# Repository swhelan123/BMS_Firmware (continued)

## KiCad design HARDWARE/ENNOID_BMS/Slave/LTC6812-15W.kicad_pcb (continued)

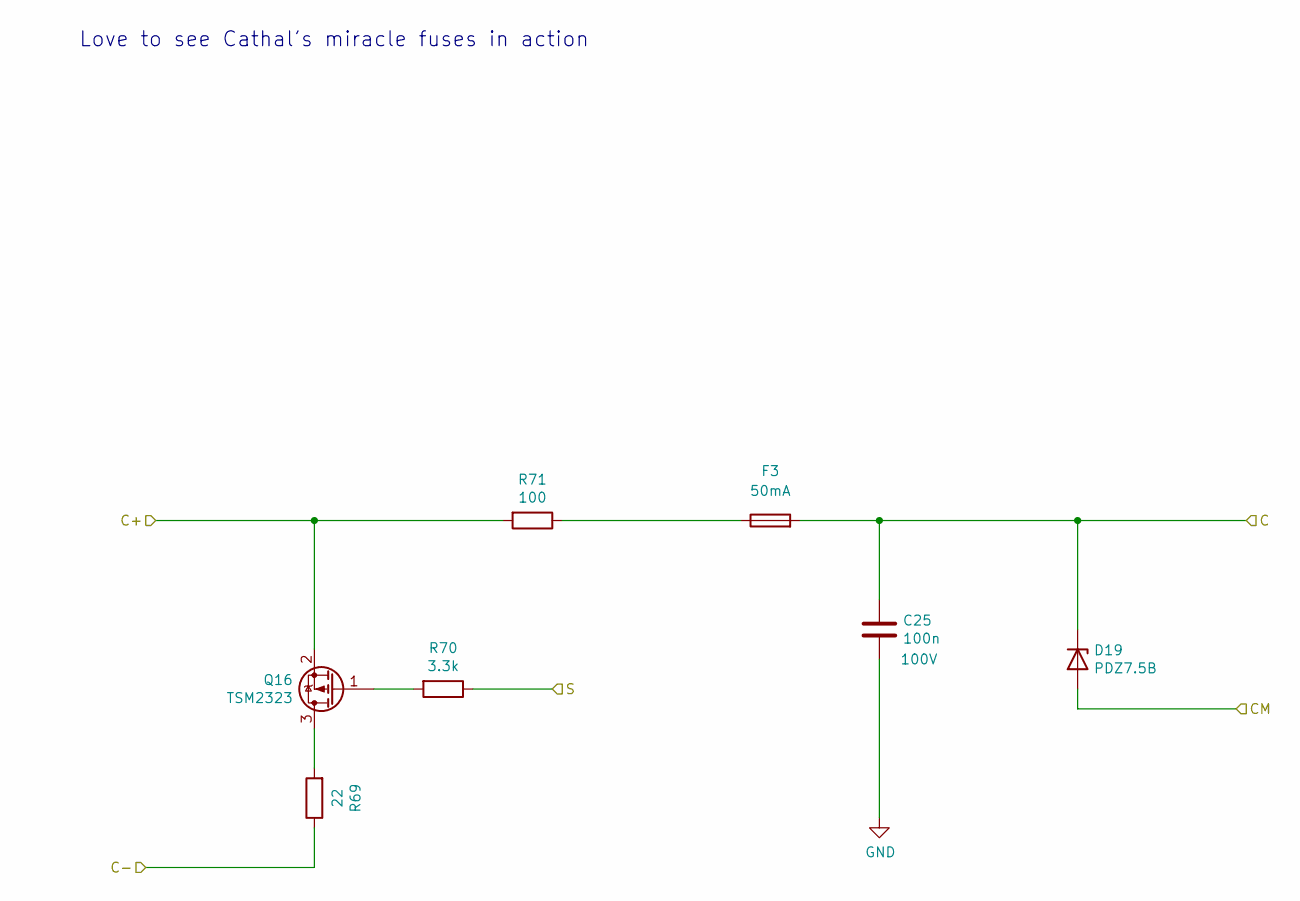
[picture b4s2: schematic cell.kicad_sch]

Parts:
C25: 100n; C_0603_1608Metric; Voltage 100V; Part Number GRM188R72A104KA35D
D19: PDZ7.5B; D_SOD-323; Part Number PDZ7.5B
F3: 50mA; Fuse_1206_3216Metric; Part Number 3413.0002.11
Q16: TSM2323; SOT-23; Part Number TSM2323CX RFG
R69: 22; R_2512_6332Metric; Part Number AC2512JK-7W22RL
R70: 3.3k; R_0508_1220Metric; Part Number WK73R2ATTD3301F
R71: 100; R_0805_2012Metric; Part Number CRCW0805100RFKEAHP

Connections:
/cell14/C: D19.2 (A); also elsewhere on the board
/cell15/C: C25.2, D19.1 (K), F3.2; also elsewhere on the board
/cell15/S: R70.1; also elsewhere on the board
Cell_1-: C25.1; also elsewhere on the board
Cell_14+: R69.1; also elsewhere on the board
Cell_15+: Q16.2 (S), R71.2; also elsewhere on the board
unnamed: F3.1, R71.1
unnamed: Q16.3 (D), R69.2
unnamed: Q16.1 (G), R70.2

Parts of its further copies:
C11, C12, C13, C14, C15, C16, C17, C18, C19, C20, C21, C22, C23, C24: 100n; C_0603_1608Metric; Voltage 100V; Part Number GRM188R72A104KA35D
D5, D6, D7, D8, D9, D10, D11, D12, D13, D14, D15, D16, D17, D18: PDZ7.5B; D_SOD-323; Part Number PDZ7.5B
F5, F7, F9, F11, F13, F15, F20, F22, F24, F26, F28, F30, F32, F34: 50mA; Fuse_1206_3216Metric; Part Number 3413.0002.11
Q2, Q3, Q4, Q5, Q6, Q7, Q8, Q9, Q10, Q11, Q12, Q13, Q14, Q15: TSM2323; SOT-23; Part Number TSM2323CX RFG
R13, R17, R21, R25, R29, R33, R37, R41, R45, R49, R53, R57, R61, R65: 22; R_2512_6332Metric; Part Number AC2512JK-7W22RL
R14, R18, R22, R26, R30, R34, R38, R42, R46, R50, R54, R58, R62, R66: 3.3k; R_0508_1220Metric; Part Number WK73R2ATTD3301F
R15, R19, R23, R27, R31, R35, R39, R43, R47, R51, R55, R59, R63, R67: 100; R_0805_2012Metric; Part Number CRCW0805100RFKEAHP

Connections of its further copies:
/cell1/C: C11.2, D5.1 (K), D6.2 (A), F34.2; also elsewhere on the board
/cell1/S: R14.1; also elsewhere on the board
/cell2/C: C12.2, D6.1 (K), D7.2 (A), F32.2; also elsewhere on the board
/cell2/S: R18.1; also elsewhere on the board
/cell3/C: C13.2, D7.1 (K), D8.2 (A), F30.2; also elsewhere on the board
/cell3/S: R22.1; also elsewhere on the board
/cell4/C: C14.2, D8.1 (K), D9.2 (A), F28.2; also elsewhere on the board
/cell4/S: R26.1; also elsewhere on the board
/cell5/C: C15.2, D9.1 (K), D10.2 (A), F26.2; also elsewhere on the board
/cell5/S: R30.1; also elsewhere on the board
/cell6/C: C16.2, D10.1 (K), D11.2 (A), F24.2; also elsewhere on the board
/cell6/S: R34.1; also elsewhere on the board
/cell7/C: C17.2, D11.1 (K), D12.2 (A), F22.2; also elsewhere on the board
/cell7/S: R38.1; also elsewhere on the board
/cell8/C: C18.2, D12.1 (K), D13.2 (A), F20.2; also elsewhere on the board
/cell8/S: R42.1; also elsewhere on the board
/cell9/S: R46.1; also elsewhere on the board
/cell10/C: C20.2, D14.1 (K), D15.2 (A), F13.2; also elsewhere on the board
/cell10/CM: C19.2, D13.1 (K), D14.2 (A), F15.2; also elsewhere on the board
/cell10/S: R50.1; also elsewhere on the board
/cell11/C: C21.2, D15.1 (K), D16.2 (A), F11.2; also elsewhere on the board
/cell11/S: R54.1; also elsewhere on the board
/cell12/C: C22.2, D16.1 (K), D17.2 (A), F9.2; also elsewhere on the board
/cell12/S: R58.1; also elsewhere on the board
/cell13/C: C23.2, D17.1 (K), D18.2 (A), F7.2; also elsewhere on the board
/cell13/S: R62.1; also elsewhere on the board
/cell14/C: C24.2, D18.1 (K), F5.2; also elsewhere on the board
/cell14/S: R66.1; also elsewhere on the board
Cell_1+: Q2.2 (S), R15.2, R17.1; also elsewhere on the board
Cell_1-: C11.1, C12.1, C13.1, C14.1, C15.1, C16.1, C17.1, C18.1, C19.1, C20.1, C21.1, C22.1, C23.1, C24.1, D5.2 (A), R13.1; also elsewhere on the board
Cell_2+: Q3.2 (S), R19.2, R21.1; also elsewhere on the board
Cell_3+: Q4.2 (S), R23.2, R25.1; also elsewhere on the board
Cell_4+: Q5.2 (S), R27.2, R29.1; also elsewhere on the board
Cell_5+: Q6.2 (S), R31.2, R33.1; also elsewhere on the board
Cell_6+: Q7.2 (S), R35.2, R37.1; also elsewhere on the board
Cell_7+: Q8.2 (S), R39.2, R41.1; also elsewhere on the board
Cell_8+: Q9.2 (S), R43.2, R45.1; also elsewhere on the board
Cell_9+: Q10.2 (S), R47.2, R49.1; also elsewhere on the board
Cell_10+: Q11.2 (S), R51.2, R53.1; also elsewhere on the board
Cell_11+: Q12.2 (S), R55.2, R57.1; also elsewhere on the board
Cell_12+: Q13.2 (S), R59.2, R61.1; also elsewhere on the board
Cell_13+: Q14.2 (S), R63.2, R65.1; also elsewhere on the board
Cell_14+: Q15.2 (S), R67.2; also elsewhere on the board
unnamed: F5.1, R67.1
unnamed: F7.1, R63.1
unnamed: F9.1, R59.1
unnamed: F11.1, R55.1
unnamed: F13.1, R51.1
unnamed: F15.1, R47.1
unnamed: F20.1, R43.1
unnamed: F22.1, R39.1
unnamed: F24.1, R35.1
unnamed: F26.1, R31.1
unnamed: F28.1, R27.1
unnamed: F30.1, R23.1
unnamed: F32.1, R19.1
unnamed: F34.1, R15.1
unnamed: Q2.3 (D), R13.2
unnamed: Q2.1 (G), R14.2
unnamed: Q3.3 (D), R17.2
unnamed: Q3.1 (G), R18.2
unnamed: Q4.3 (D), R21.2
unnamed: Q4.1 (G), R22.2
unnamed: Q5.3 (D), R25.2
unnamed: Q5.1 (G), R26.2
unnamed: Q6.3 (D), R29.2
unnamed: Q6.1 (G), R30.2
unnamed: Q7.3 (D), R33.2
unnamed: Q7.1 (G), R34.2
unnamed: Q8.3 (D), R37.2
unnamed: Q8.1 (G), R38.2
unnamed: Q9.3 (D), R41.2
unnamed: Q9.1 (G), R42.2
unnamed: Q10.3 (D), R45.2
unnamed: Q10.1 (G), R46.2
unnamed: Q11.3 (D), R49.2
unnamed: Q11.1 (G), R50.2
unnamed: Q12.3 (D), R53.2
unnamed: Q12.1 (G), R54.2
unnamed: Q13.3 (D), R57.2
unnamed: Q13.1 (G), R58.2
unnamed: Q14.3 (D), R61.2
unnamed: Q14.1 (G), R62.2
unnamed: Q15.3 (D), R65.2
unnamed: Q15.1 (G), R66.2

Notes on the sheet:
Love to see Cathal's miracle fuses in action

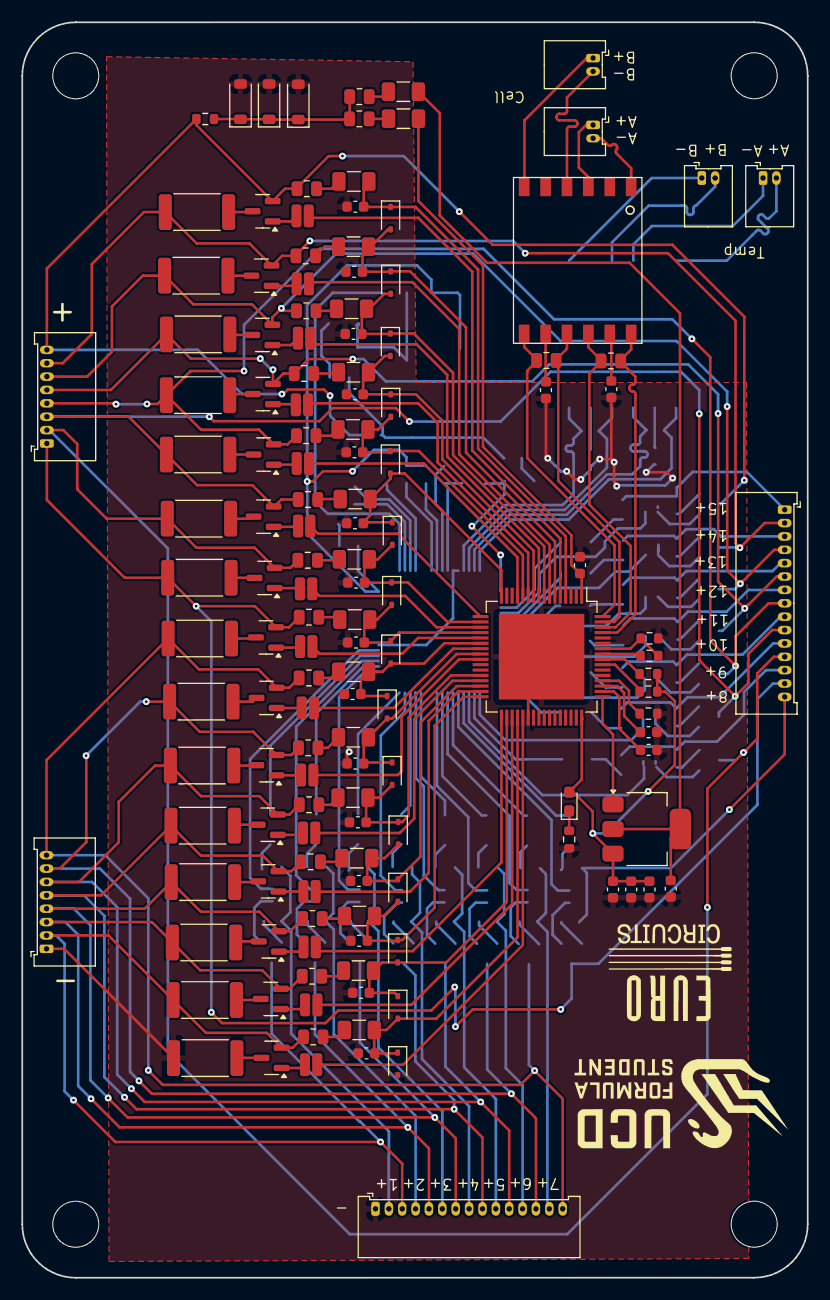
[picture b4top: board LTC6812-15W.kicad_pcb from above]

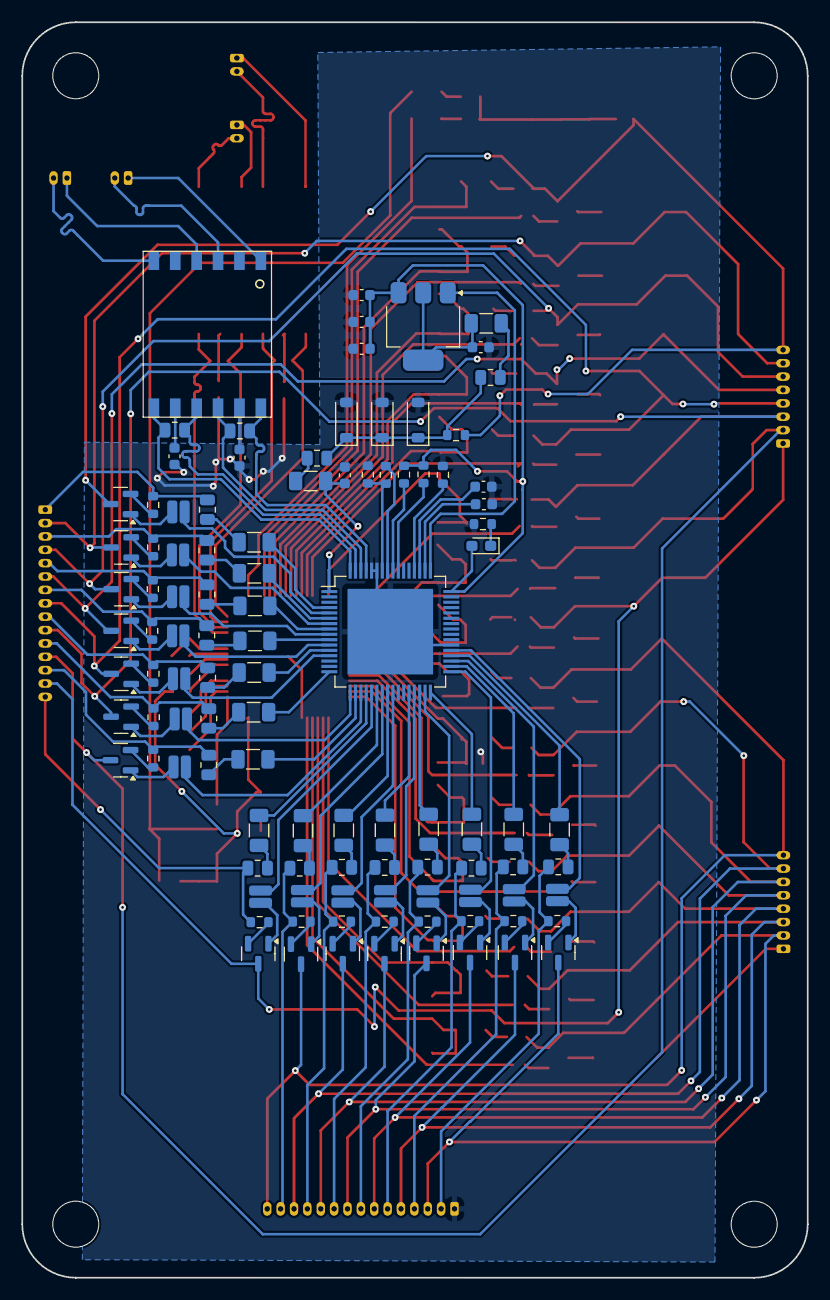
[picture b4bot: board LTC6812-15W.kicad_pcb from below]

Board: 2 copper layers, 73.4 x 117.4 mm, 246 parts (104 on the bottom side), 231 nets.

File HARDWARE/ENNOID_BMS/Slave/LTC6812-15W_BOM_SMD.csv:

Reference,Qty,Value,DNP,Footprint,Datasheet,Part Number
"C1,C4,C10,C11,C12,C13,C14,C15,C16,C17,C18,C19,C20,C21,C22,C23,C24,C25,C28",19,100n,,Capacitor_SMD:C_0603_1608Metric,https://pim.murata.com/asset/pim4/ceramicCapacitorSMD/GRM188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,GRM188R72A104KA35D
"C2,C3,C5,C6,C7,C26,C27,C29,C30,C31",10,1uF,,Capacitor_SMD:C_0603_1608Metric,https://mm.digikey.com/Volume0/opasdata/d220001/medias/docus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,CL10B105KP8NNNC
"C8,C9,C32,C33",4,100p,,Capacitor_SMD:C_0603_1608Metric,https://pim.murata.com/asset/pim4/ceramicCapacitorSMD/GRM188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,GRM1885C1H101JA01D
"D1,D2,D20,D21",4,1N4148W,,Diode_SMD:D_SOD-123,https://www.mouser.ie/datasheet/3/175/1/BAV16W_1N4148W.pdf,1N4148W-7-F
"D3,D22",2,MMSZ5268BT1G,,Diode_SMD:D_SOD-123,https://www.onsemi.com/pub/Collateral/MMSZ5221BT1-D.PDF,MMSZ5268BT1G
"D4,D23",2,LED,,LED_SMD:LED_0603_1608Metric_Pad1.05x0.95mm_HandSolder,https://www.vishay.com/doc?84393,VLMTG1400-GS08
"D5,D6,D7,D8,D9,D10,D11,D12,D13,D14,D15,D16,D17,D18,D19",15,PDZ7.5B,,Diode_SMD:D_SOD-323,https://assets.nexperia.com/documents/data-sheet/PDZ-B_SER.pdf,PDZ7.5B
"F1,F2,F3,F20,F21,F22,F23,F24,F25,F26,F27,F28,F29,F30,F31,F32",16,5A,,ENNOID:FUSC10948X488N,https://4donline.ihs.com/images/VipMasterIC/IC/LFSI/LFSI-S-A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,0885005.DR
"FB1,FB2",2,33,,Resistor_SMD:R_0603_1608Metric,https://www.mouser.ie/datasheet/3/76/1/ENFA0003.pdf,BLM18PG330SN1D
"Q1,Q17",2,DZTT5551,,Package_TO_SOT_SMD:SOT-223,https://www.mouser.ie/datasheet/3/175/1/ds31219.pdf,DZT5551-13
"Q2,Q3,Q4,Q5,Q6,Q7,Q8,Q9,Q10,Q11,Q12,Q13,Q14,Q15,Q16",15,TSM2323,,Package_TO_SOT_SMD:SOT-23,https://www.taiwansemi.com/assets/datasheet/pdf.php?pn=TSM2323CX,TSM2323
"Q18,Q19,Q20,Q21,Q22,Q23,Q24,Q25,Q26,Q27,Q28,Q29,Q30,Q31,Q32",15,2N7002,,Package_TO_SOT_SMD:SOT-23,https://www.onsemi.com/pub/Collateral/NDS7002A-D.PDF,2N7002
"R1,R3,R8,R9,R15,R19,R23,R27,R31,R35,R39,R43,R47,R51,R55,R59,R63,R67,R71,R74,R76,R81,R82,R84,R85,R86,R87,R88,R89,R90,R91,R92,R93,R94,R95,R96,R98,R99",38,100,,Resistor_SMD:R_0603_1608Metric,https://www.vishay.com/docs/20035/dcrcwe3.pdf,CRCW0603100RFKEA
"R2,R75",2,806,,Resistor_SMD:R_0603_1608Metric,https://www.vishay.com/docs/20035/dcrcwe3.pdf,CRCW0603806RFKEA
"R4,R77",2,1M,,Resistor_SMD:R_0603_1608Metric,https://www.vishay.com/docs/20035/dcrcwe3.pdf,CRCW06031M00FKEA
"R5,R10,R78,R83",4,1.2k,,Resistor_SMD:R_0603_1608Metric,https://www.vishay.com/docs/20035/dcrcwe3.pdf,CRCW06031K20FKEA
"R6,R7,R79,R80",4,0,,Resistor_SMD:R_0603_1608Metric,https://www.vishay.com/docs/20035/dcrcwe3.pdf,CRCW06030000Z0EA
"R11,R12,R16,R20,R24,R28,R32,R36,R40,R44,R48,R52,R56,R60,R64",15,680,,Resistor_SMD:R_0603_1608Metric,https://www.vishay.com/docs/20035/dcrcwe3.pdf,CRCW0603680RFKEA
"R13,R17,R21,R25,R29,R33,R37,R41,R45,R49,R53,R57,R61,R65,R69",15,22,,Resistor_SMD:R_2512_6332Metric,https://www.mouser.ie/datasheet/3/508/1/PYu-AC_51_RoHS_L_11.pdf,AC2512JK-7W22RL
"R14,R18,R22,R26,R30,R34,R38,R42,R46,R50,R54,R58,R62,R66,R68,R70,R72,R73,R97,R100,R101,R102,R103,R104,R105,R106,R107,R108,R109,R110",30,3.3k,,Resistor_SMD:R_0603_1608Metric,https://www.vishay.com/docs/20035/dcrcwe3.pdf,CRCW06033K30FKEA
"TR1,TR2",2,HM2102NL,,ENNOID:HM2102NL,https://www.mouser.ie/datasheet/3/508/1/HM2102NL.pdf,HM2102NL
"U1,U2",2,LTC6812-1,,ENNOID:TQFP-64-1EP_10x10mm_P0.5mm_EP8x8mm,https://www.analog.com/media/en/technical-documentation/data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,LTC6812-1

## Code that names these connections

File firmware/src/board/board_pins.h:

/* board_pins.h — STM32F303VC pin assignments for this hardware revision.
 *
 * Conventions:
 *   GPIOx_PIN_n  where x = port letter, n = pin number
 *   _AF_n        alternate function number (from STM32F303 datasheet Table 14)
 *
 * OQ items are OPEN QUESTION fields still awaiting hardware confirmation.
 */
#pragma once

/* ── SPI1 — shared isoSPI bus ─────────────────────────────────────────────── */
#define SPI_PORT            GPIOA
#define SPI_SCK_PIN         5u      /* PA5  — AF5: SPI1_SCK  */
#define SPI_MISO_PIN        6u      /* PA6  — AF5: SPI1_MISO */
#define SPI_MOSI_PIN        7u      /* PA7  — AF5: SPI1_MOSI */
#define SPI_AF              5u

/* ── SPI1 chip-selects (manual GPIO, active-low, idle HIGH) ──────────────── */
#define CS_CELL_PORT        GPIOA
#define CS_CELL_PIN         4u      /* PA4  — CS for CELL-chain LTC6820 */

#define CS_TEMP_PORT        GPIOB
#define CS_TEMP_PIN         12u     /* PB12 — CS for TEMP-chain LTC6820 */

/* ── USART2 — USB-serial bridge (CP2104) ─────────────────────────────────── */
#define UART_PORT           GPIOA
#define UART_TX_PIN         2u      /* PA2  — AF7: USART2_TX */
#define UART_RX_PIN         3u      /* PA3  — AF7: USART2_RX */
#define UART_AF             7u

/* ── I2C2 — ISL28022 power monitor ───────────────────────────────────────── */
#define I2C_PORT            GPIOA
#define I2C_SCL_PIN         9u      /* PA9  — AF4: I2C2_SCL */
#define I2C_SDA_PIN         10u     /* PA10 — AF4: I2C2_SDA */
#define I2C_AF              4u

/* ISL28022 I2C address: A0 and A1 pins are unconnected (float → pulled low).
 * Default address = 0x40 (A1=0, A0=0). Verify on board before first I2C test. */
#define ISL28022_I2C_ADDR   (0x40u)

/* ── ADC1 — Vpack load-side voltage ─────────────────────────────────────── */
#define VPACK_ADC_PORT      GPIOA
#define VPACK_ADC_PIN       1u      /* PA1  — ADC1_IN2 */
#define VPACK_ADC_CHANNEL   2u
#define VPACK_VREF_MV       3300u

/* ── CAN — vehicle bus (ISO1050) ─────────────────────────────────────────── */
#define CAN_PORT            GPIOA
#define CAN_RX_PIN          11u     /* PA11 — AF9: CAN_RX */
#define CAN_TX_PIN          12u     /* PA12 — AF9: CAN_TX */
#define CAN_AF              9u

/* ── Permission outputs ───────────────────────────────────────────────────── */
/* All four permission outputs (PB10/PB11/PB0/PB2) drive downstream shutdown
 * logic through identical N-channel MOSFET stages (confirmed from schematic):
 *   MCU HIGH → MOSFET on → drain pulled LOW → downstream active-low signal asserted.
 *   MCU LOW  → MOSFET off → downstream pulled HIGH → signal inactive (safe).
 * Safe default at reset = all MCU LOW (board_outputs_init_safe() enforces this). */
#define OUTPUT_PORT_B           GPIOB

#define PIN_CHARGE_ENABLE       0u   /* PB0  — Charge permission output       */
#define PIN_LED0                1u   /* PB1  — Status LED                     */
#define PIN_CHARGER_SAFETY      2u   /* PB2  — Charger safety output          */
#define PIN_POWER_LED           3u   /* PB3  — Power/status LED               */
#define PIN_POWER_ENABLE        5u   /* PB5  — Power latch (keep-alive)       */
#define PIN_DISCHARGE_ENABLE    10u  /* PB10 — Discharge permission; active-low downstream */
#define PIN_MASTER_OK           11u  /* PB11 — MasterOk / multipurpose;       active-low downstream */

/* ── Digital inputs ───────────────────────────────────────────────────────── */
#define PIN_POWER_BUTTON        4u   /* PB4  — Power button (input)           */

#define CHARGE_DETECT_PORT      GPIOC
#define PIN_CHARGE_DETECT       14u  /* PC14 — Charger present (input)        */

/* ── Debug — SWD ──────────────────────────────────────────────────────────── */
/* PA13 SWDIO, PA14 SWCLK — handled by debugger; never configure as GPIO */

/* ── HSE crystal ──────────────────────────────────────────────────────────── */
/* PF0/PF1 OSC_IN/OSC_OUT — configured by RCC; not GPIO */
  

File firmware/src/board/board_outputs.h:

/* board_outputs.h — permission output API.
 *
 * This is the ONLY module that calls the MCU GPIO set functions for permission
 * outputs. All other modules call board_outputs_set_*() via this API.
 *
 * Output semantics (STM32F303VC MCU-level, confirmed from schematic):
 *   All four permission outputs (PB10/PB11/PB0/PB2) share the same MOSFET model:
 *     MCU HIGH → MOSFET on → downstream LOW → permission ACTIVE.
 *     MCU LOW  → MOSFET off → downstream HIGH → permission INACTIVE (safe).
 *   PB5 (PowerEnable): HIGH keeps board alive; LOW releases power latch.
 *   PB1 (LED0), PB3 (PowerLED): HIGH = LED on.
 *
 * Safe default: all permission outputs at MCU LOW (downstream inactive).
 */
#pragma once
#include <stdbool.h>
#include "bms_types.h"

/* Initialise permission GPIOs to safe (inactive) state. Must be the first
 * board function called on any power-up or reset path. */
void board_outputs_init_safe(void);

/* Individual permission setters. True = permission active; false = inactive.
 * Each function encodes the MCU-level polarity for the downstream circuit. */
void board_outputs_set_master_ok(bool allowed);
void board_outputs_set_discharge_permission(bool allowed);
void board_outputs_set_charge_permission(bool allowed);
void board_outputs_set_charger_safety(bool allowed);

/* Power latch — call board_outputs_release_power() only after all permission
 * outputs have been deasserted and the shutdown sequence is complete. */
void board_outputs_assert_power_enable(void);
void board_outputs_release_power(void);

/* Status LEDs */
void board_outputs_set_led0(bool on);
void board_outputs_set_power_led(bool on);

/* Emergency safe-state: deasserts all permission outputs in one call.
 * Called from fatal fault paths and the IWDG reset vector. */
void board_outputs_disable_all(void);

/* Read-back current logical output state (not MCU pin level). */
BmsOutputsBitmask board_outputs_get_state(void);

/* ── Read-only GPIO snapshot for bring-up diagnostics ─────────────────────── */
/* Reads raw MCU input data registers — no writes, no side effects.
 * All fields are raw MCU pin levels (0 or 1). */
typedef struct {
    uint8_t cs_cell;          /* PA4  — CS CELL chain (idle=1, active=0) */
    uint8_t cs_temp;          /* PB12 — CS TEMP chain (idle=1, active=0) */
    uint8_t power_button;     /* PB4  — Power button input */
    uint8_t charge_detect;    /* PC14 — Charger present input */
    uint8_t power_enable;     /* PB5  — Power latch raw MCU level */
    uint8_t master_ok_raw;    /* PB11 — MasterOk raw MCU level */
    uint8_t discharge_raw;    /* PB10 — Discharge_enable raw MCU level */
    uint8_t charge_raw;       /* PB0  — Charge permission raw MCU level */
    uint8_t charger_safety_raw; /* PB2 — ChargerSafety raw MCU level */
} BmsGpioSnapshot;

void board_outputs_get_gpio_snapshot(BmsGpioSnapshot *out);

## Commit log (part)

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2026-05-16 feat: add desktop tool backend CLI and GUI shell
2026-05-16 feat: add local demo and bootloader update simulation
2026-05-16 feat: add one-shot measurement pipeline
2026-05-16 feat: complete openwire and balance safety paths
2026-05-16 feat: improve GUI for pre-hardware bring-up
2026-05-16 chore: add pre-hardware setup demo and release scripts
2026-05-17 docs: add first-flash readiness package
2026-05-17 feat: implement I2C power monitor path and Enepaq table
2026-05-17 feat: implement real bootloader protocol build
2026-05-17 feat: add live fake hardware simulator
2026-05-17 feat: polish GUI and add editable config editor
2026-05-20 docs: align documentation with prehardware software state
2026-06-09 added SOC
2026-06-12 Use LiveFakeHardware for live modes
    Make fake-target handling aware of live vs static simulation modes. Update scripts/run_gui.sh usage text with separate live/static mode lists and improve --mode extraction to handle hyphenated names.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
